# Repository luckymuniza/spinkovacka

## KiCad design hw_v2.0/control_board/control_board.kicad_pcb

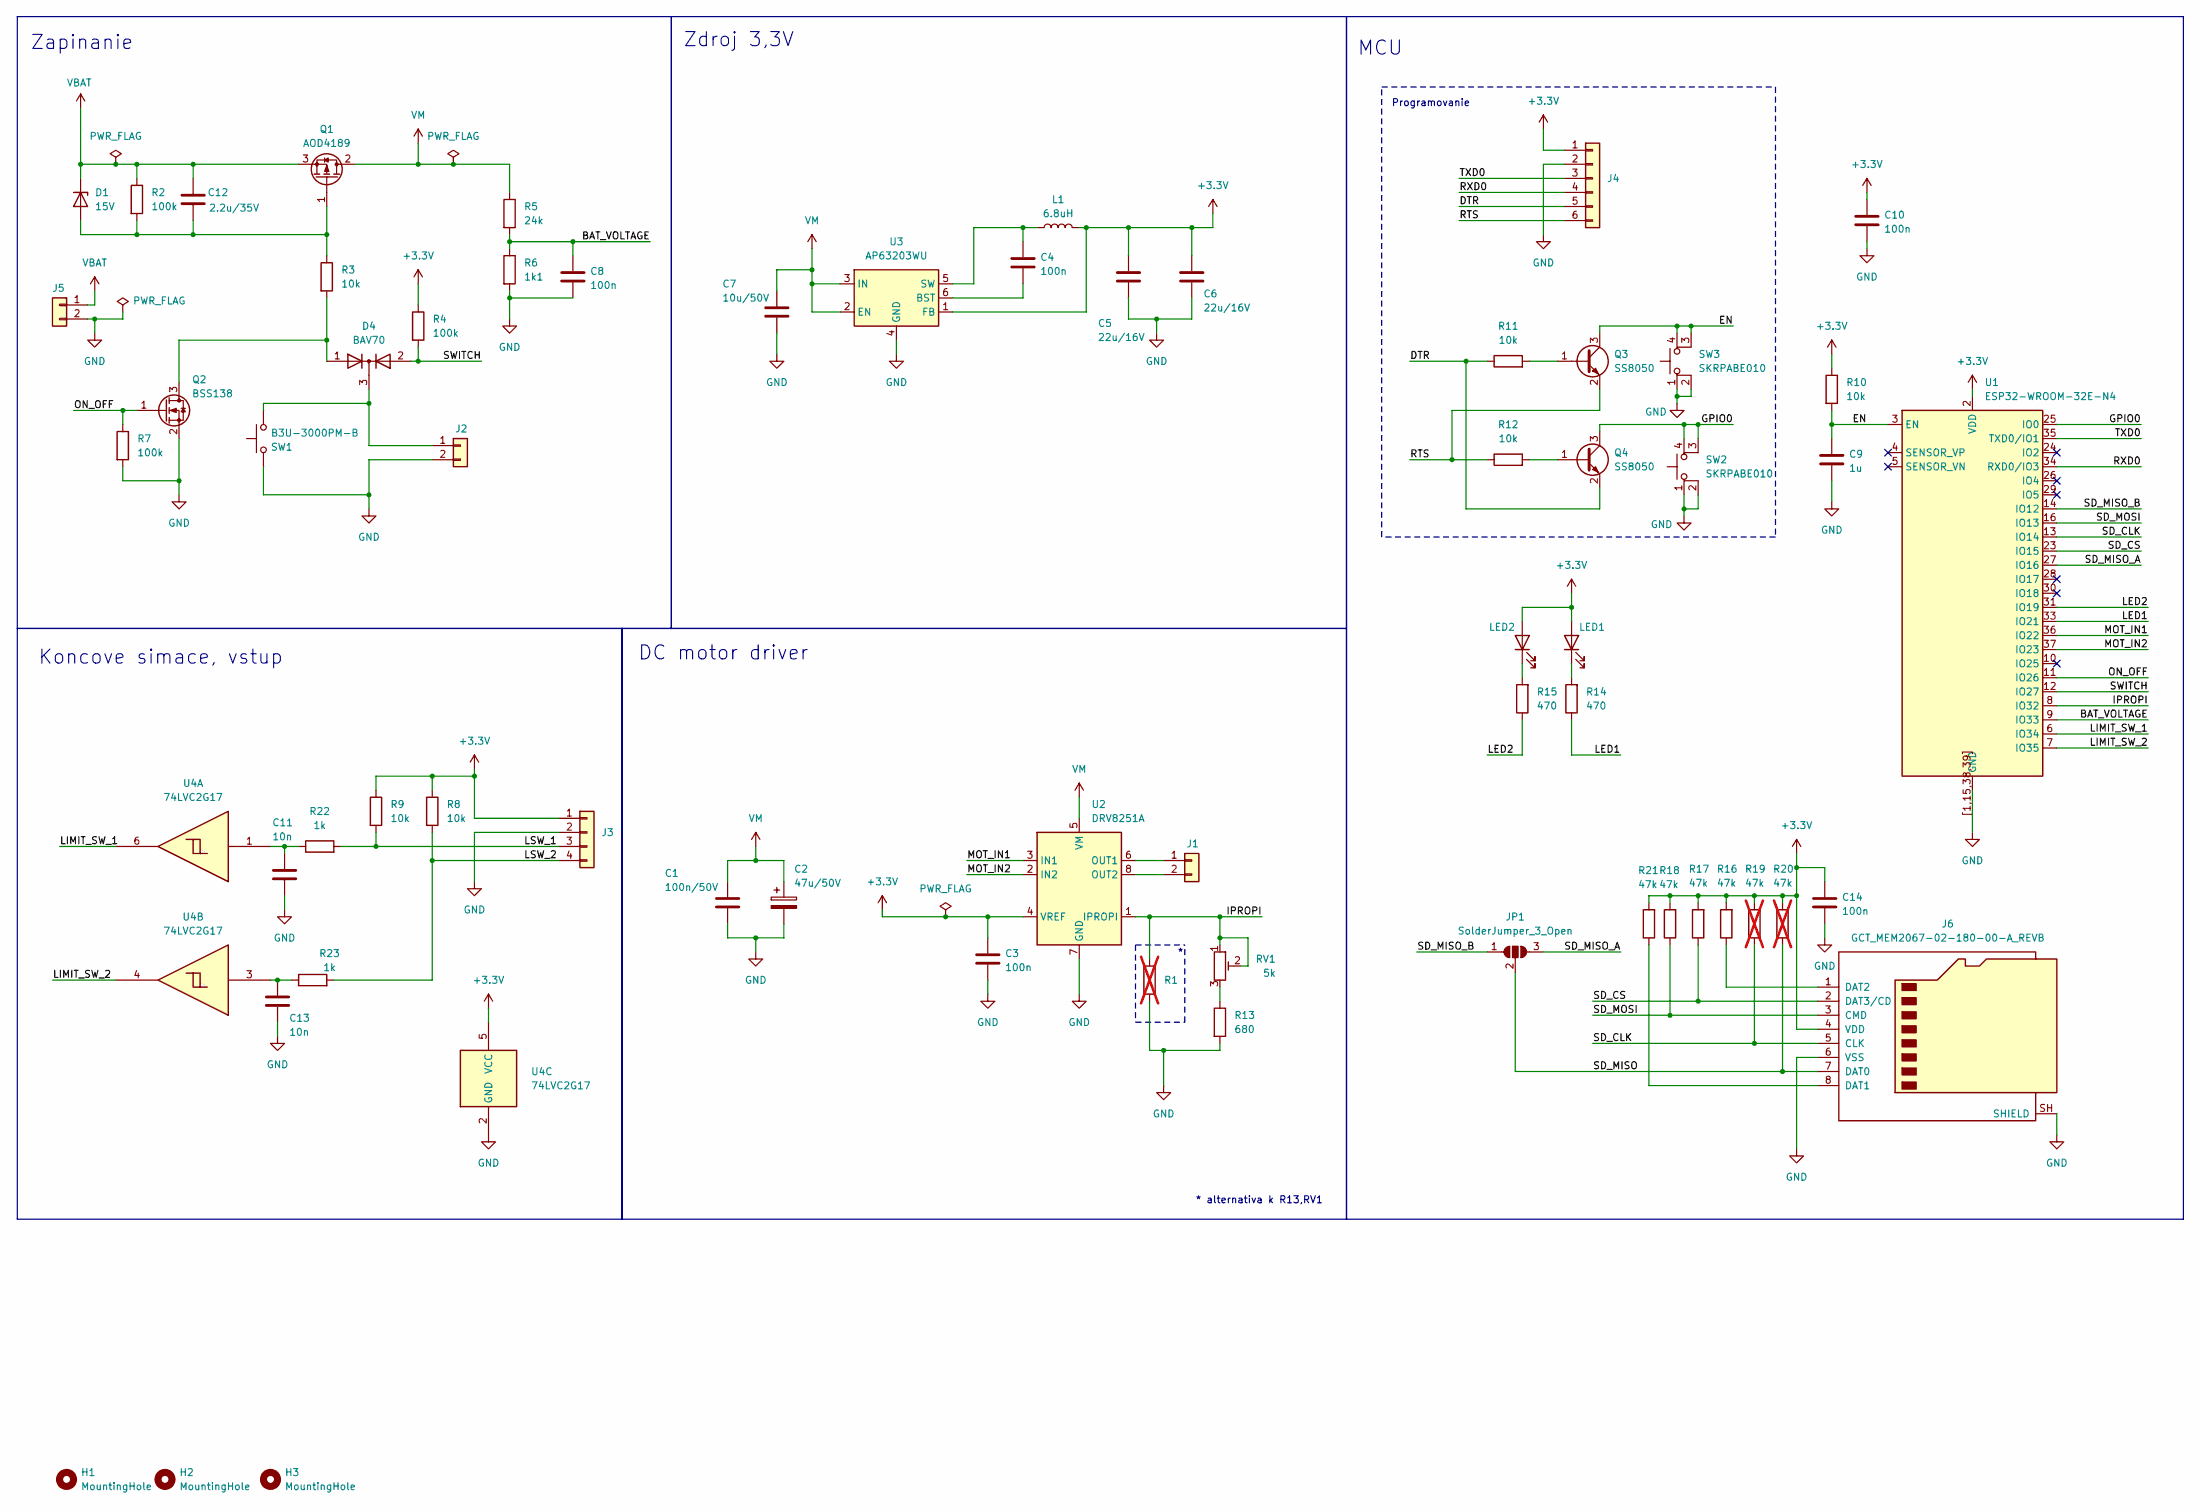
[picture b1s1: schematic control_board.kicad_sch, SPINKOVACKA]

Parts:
C1: 100n/50V; C_1206_3216Metric
C2: 47u/50V; CP_Elec_6.3x5.8
C3, C4, C8, C10: 100n; C_1206_3216Metric
C5, C6: 22u/16V; C_1206_3216Metric
C7: 10u/50V; C_1210_3225Metric
C9: 1u; C_1206_3216Metric
C11, C13: 10n; C_0805_2012Metric
C12: 2.2u/35V; C_1206_3216Metric
C14: 100n; C_0805_2012Metric_Pad1.18x1.45mm_HandSolder
D1: 15V; Nexperia_CFP3_SOD-123W
D4: BAV70; SOT-23
H1, H2, H3: MountingHole; MountingHole_3.2mm_M3
J1: JST_XH_B2B-XH-A_1x02_P2.50mm_Vertical
J2: JST_PH_B2B-PH-K_1x02_P2.00mm_Vertical
J3: JST_PH_B4B-PH-K_1x04_P2.00mm_Vertical
J4: JST_PH_B6B-PH-K_1x06_P2.00mm_Vertical
J5: JST_VH_B2PS-VH_1x02_P3.96mm_Horizontal
J6: GCT_MEM2067-02-180-00-A_REVB
JP1: SolderJumper_3_Open; SolderJumper-3_P1.3mm_Open_RoundedPad1.0x1.5mm_NumberLabels
L1: 6.8uH; L_Panasonic_PCC-M0530M
LED1, LED2: LED_1206_3216Metric
Q1: AOD4189; TO-252-2
Q2: BSS138; SOT-23
Q3, Q4: SS8050; SOT-23
R1: 1k5; R_0805_2012Metric; not fitted
R2, R4, R7: 100k; R_0805_2012Metric
R3, R8, R9, R10, R11, R12: 10k; R_0805_2012Metric
R5: 24k; R_0805_2012Metric
R6: 1k1; R_0805_2012Metric
R13: 680; R_0805_2012Metric
R14, R15: 470; R_0805_2012Metric
R16, R17, R18, R21: 47k; R_0805_2012Metric
R19, R20: 47k; R_0805_2012Metric; not fitted
R22, R23: 1k; R_0805_2012Metric
RV1: 5k; Potentiometer_Bourns_3314J_Vertical
SW1: B3U-3000PM-B; SW_SPST_B3U-3000P-B
SW2, SW3: SKRPABE010; SW_TACT_ALPS_SKRPABE010
U1: ESP32-WROOM-32E-N4; ESP32-WROOM-32E
U2: DRV8251A; SOIC-8-1EP_3.9x4.9mm_P1.27mm_EP2.95x4.9mm_Mask2.71x3.4mm_Th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
U3: AP63203WU; TSOT-23-6
U4: 74LVC2G17; SOT-23-6

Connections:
+3.3V: C3.1, C5.1, C6.1, C10.1, C14.1, J3.1, J4.1, J6.4 (VDD), L1.2, LED1.2 (A), LED2.2 (A), R4.1, R8.1, R9.1, R10.1, R16.2, R17.2, R18.2, R19.2, R20.2, R21.2, U1.2 (VDD), U2.4 (VREF), U3.1 (FB), U4.5 (VCC)
/BAT_VOLTAGE: C8.1, R5.2, R6.1, U1.9 (IO33)
/DTR: J4.5, Q4.2 (E), R11.1
/EN: C9.1, Q3.3 (C), R10.2, SW3.3 (K), SW3.4 (A), U1.3 (EN)
/GPIO0: Q4.3 (C), SW2.3 (K), SW2.4 (A), U1.25 (IO0)
/IPROPI: R1.1, RV1.1, RV1.2, U1.8 (IO32), U2.1 (IPROPI)
/LED1: R14.1, U1.33 (IO21)
/LED2: R15.1, U1.31 (IO19)
/LIMIT_SW_1: U1.6 (IO34), U4.6
/LIMIT_SW_2: U1.7 (IO35), U4.4
/LSW_1: J3.3, R9.2, R22.2
/LSW_2: J3.4, R8.2, R23.2
/MOT_IN1: U1.36 (IO22), U2.3 (IN1)
/MOT_IN2: U1.37 (IO23), U2.2 (IN2)
/ON_OFF: Q2.1 (G), R7.1, U1.11 (IO26)
/RTS: J4.6, Q3.2 (E), R12.1
/RXD0: J4.4, U1.34 (RXD0/IO3)
/SD_CLK: J6.5 (CLK), R19.1, U1.13 (IO14)
/SD_CS: J6.2 (DAT3/CD), R17.1, U1.23 (IO15)
/SD_MISO: J6.7 (DAT0), JP1.2 (C), R20.1
/SD_MISO_A: JP1.3 (B), U1.27 (IO16)
/SD_MISO_B: JP1.1 (A), U1.14 (IO12)
/SD_MOSI: J6.3 (CMD), R18.1, U1.16 (IO13)
/SWITCH: D4.2 (A), R4.2, U1.12 (IO27)
/TXD0: J4.3, U1.35 (TXD0/IO1)
GND: C1.2, C2.2, C3.2, C5.2, C6.2, C7.2, C8.2, C9.2, C10.2, C11.2, C13.2, C14.2, J2.2, J3.2, J4.2, J5.2, J6.6 (VSS), J6.SH (SHIELD), Q2.2 (S), R1.2, R6.2, R7.2, R13.2, SW1.2, SW2.1, SW2.2, SW3.1, SW3.2, U1.1 (GND), U1.15 (GND), U1.38 (GND), U1.39 (GND), U1.[1,15,38,39] (GND), U2.7 (GND), U2.9 (GND), U3.4 (GND), U4.2 (GND)
unnamed: C11.1, R22.1, U4.1
unnamed: C13.1, R23.1, U4.3
unnamed: C12.2, D1.2 (A), Q1.1 (G), R2.2, R3.1
unnamed: D4.3 (K), J2.1, SW1.1
unnamed: J1.1, U2.6 (OUT1)
unnamed: J1.2, U2.8 (OUT2)
unnamed: J6.8 (DAT1), R21.1
unnamed: J6.1 (DAT2), R16.1
unnamed: LED1.1 (K), R14.2
unnamed: LED2.1 (K), R15.2
unnamed: D4.1 (A), Q2.3 (D), R3.2
unnamed: Q3.1 (B), R11.2
unnamed: Q4.1 (B), R12.2
unnamed: R13.1, RV1.3
unnamed: C4.2, U3.6 (BST)
unnamed: C4.1, L1.1, U3.5 (SW)
VBAT: C12.1, D1.1 (K), J5.1, Q1.3 (S), R2.1
VM: C1.1, C2.1, C7.1, Q1.2 (D), R5.1, U2.5 (VM), U3.2 (EN), U3.3 (IN)

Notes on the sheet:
MCU
Zapinanie
Zdroj 3,3V
Koncove simace, vstup
Programovanie
DC motor driver
* alternativa k R13,RV1

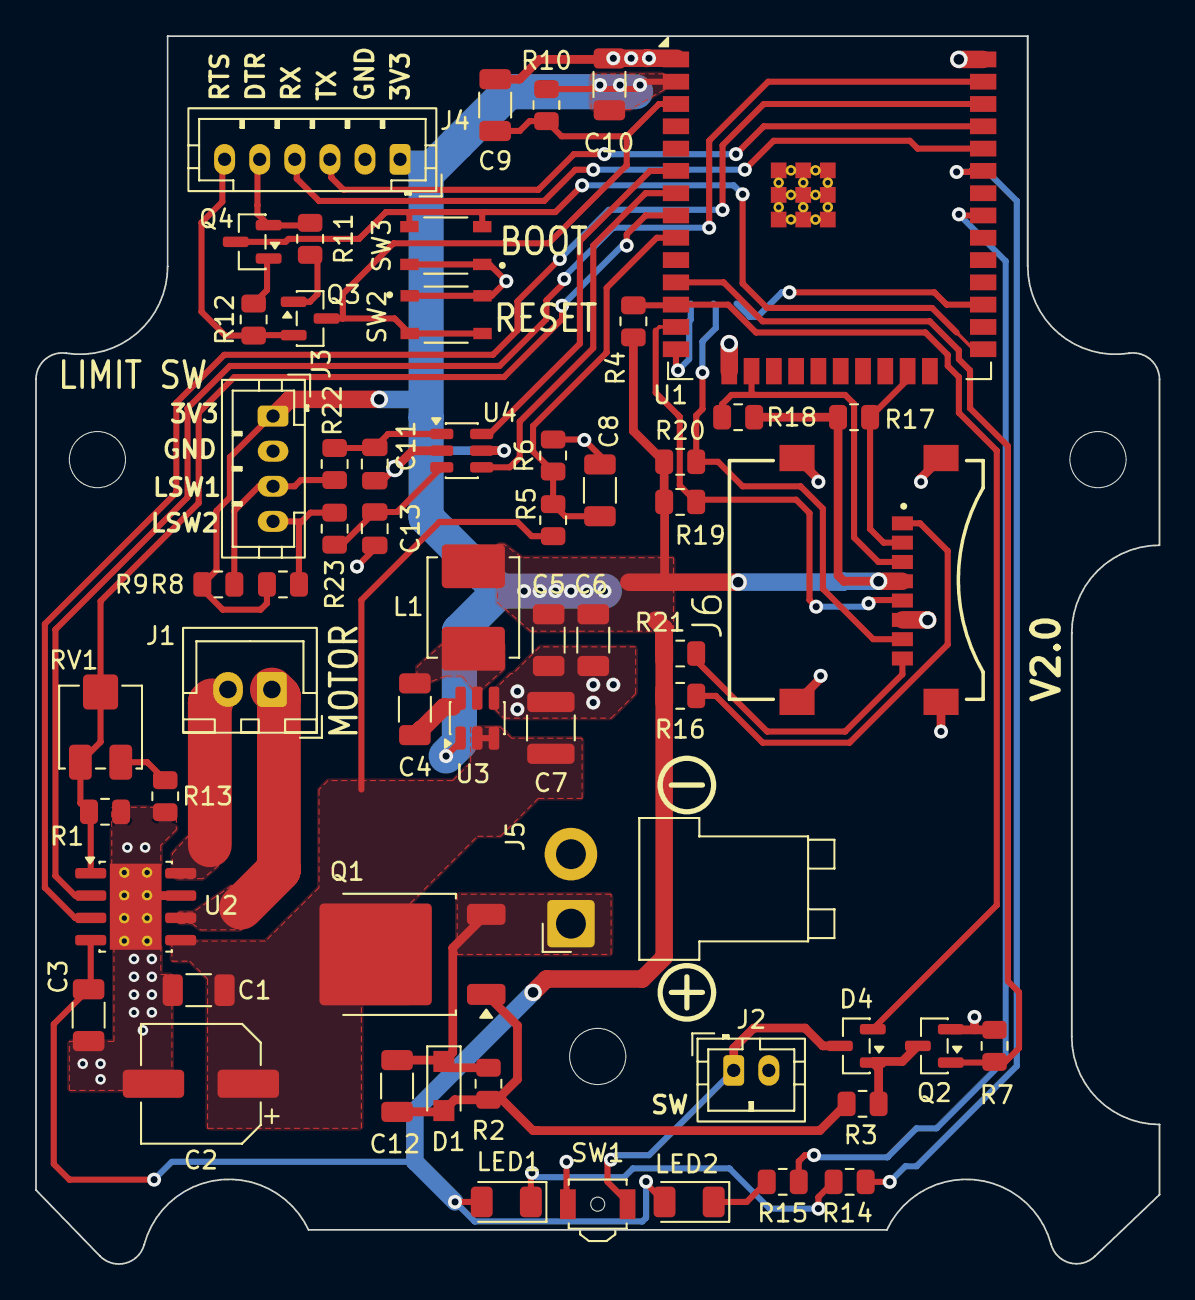
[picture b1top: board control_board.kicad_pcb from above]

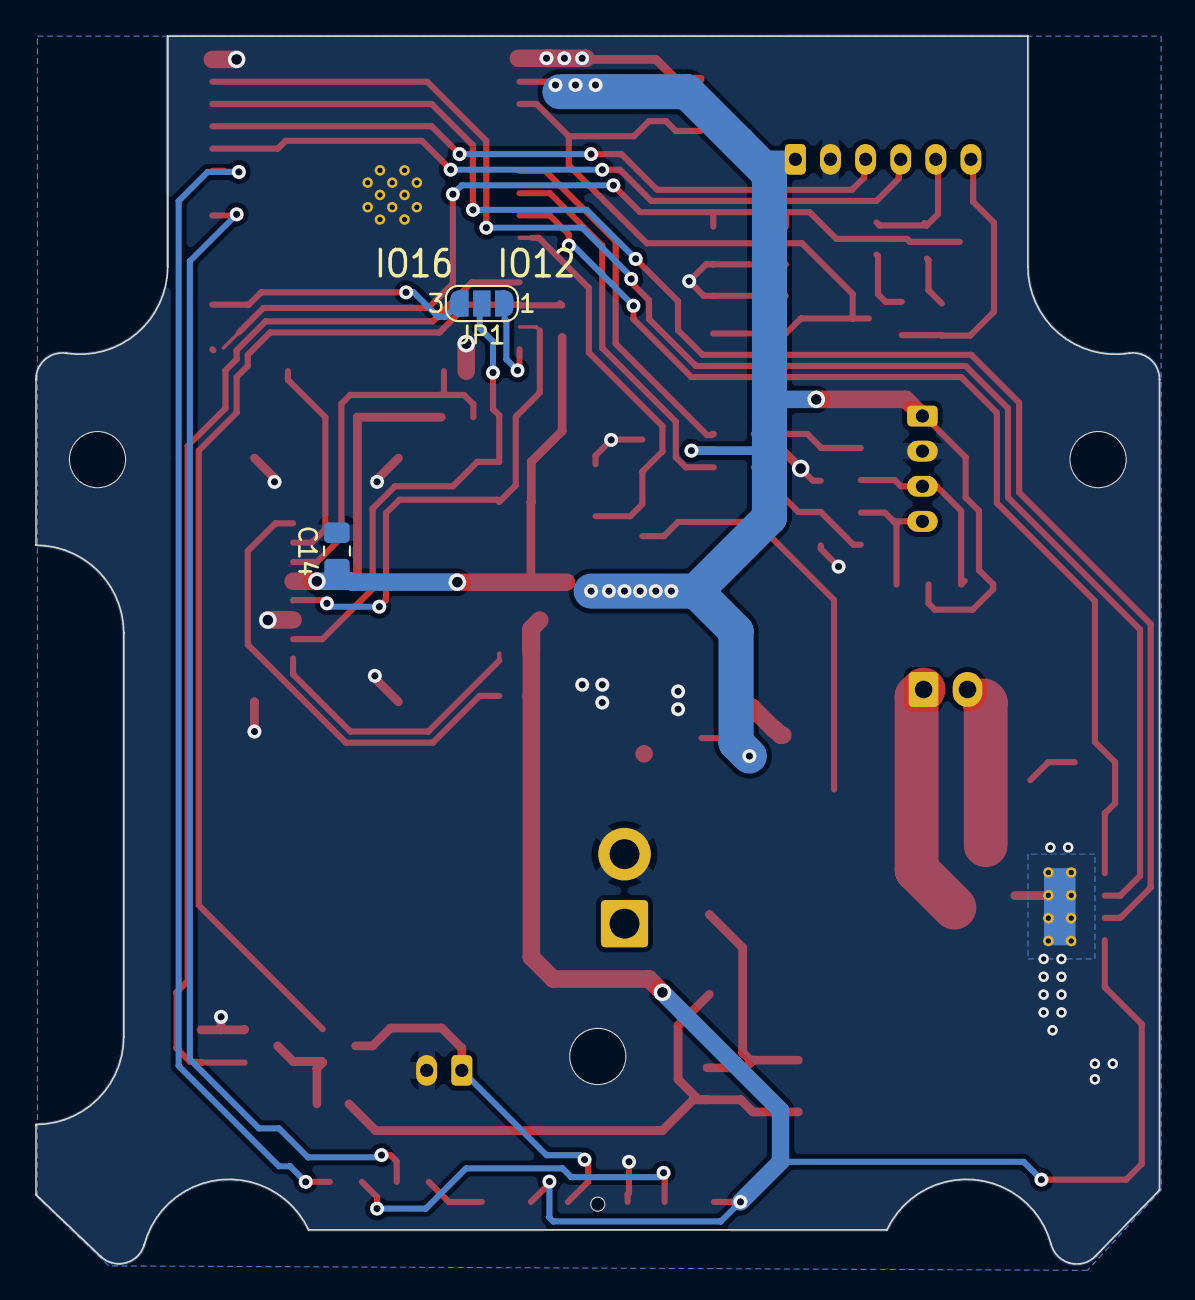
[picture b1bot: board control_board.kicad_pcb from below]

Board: 2 copper layers, 64.0 x 69.9 mm, 64 parts (2 on the bottom side), 44 nets.

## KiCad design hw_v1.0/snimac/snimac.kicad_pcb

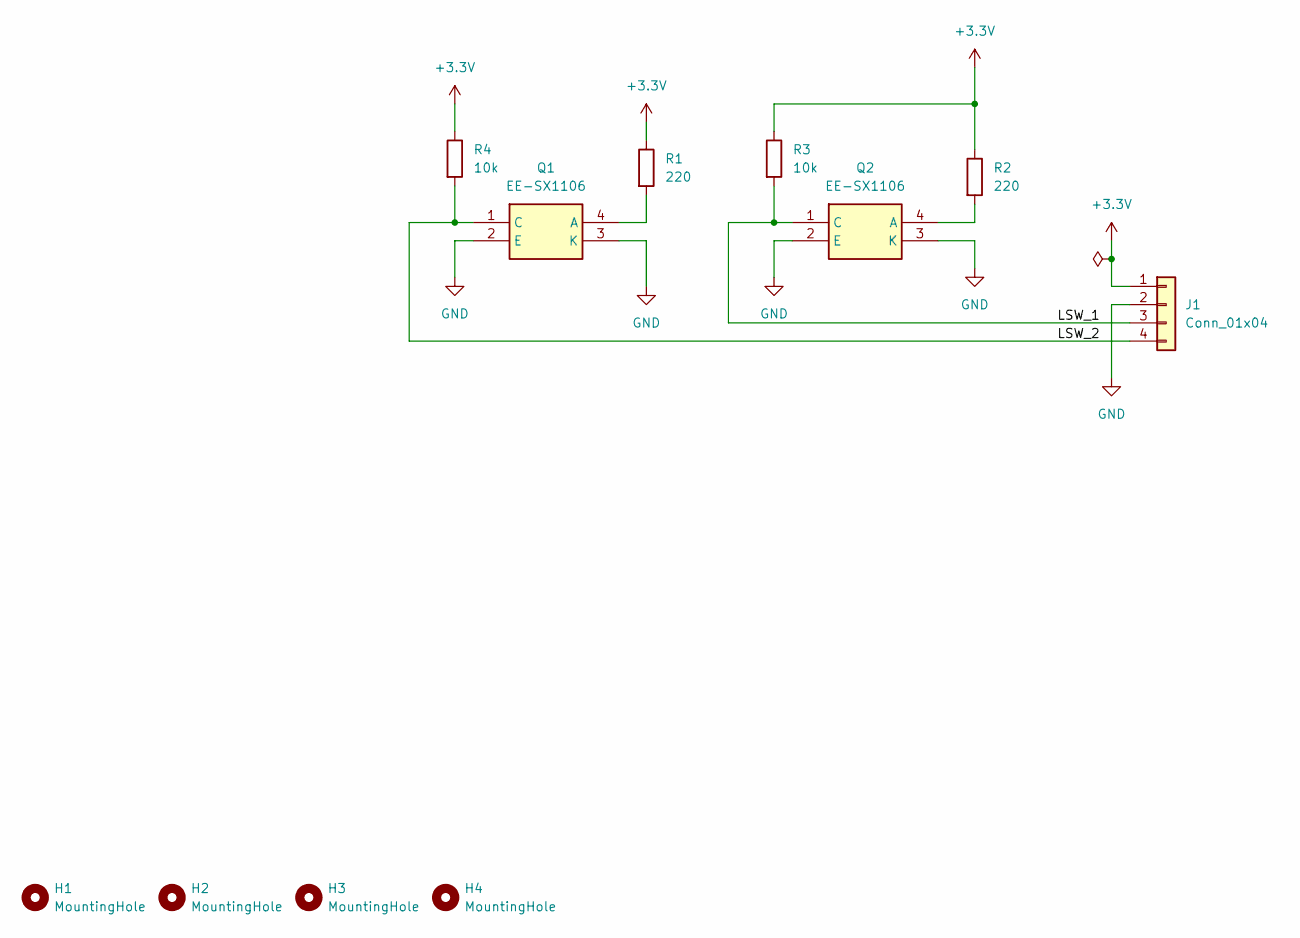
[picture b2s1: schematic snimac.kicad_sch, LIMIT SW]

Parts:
H1, H2, H3, H4: MountingHole; MountingHole_2.5mm
J1: Conn_01x04; JST_PH_B4B-PH-K_1x04_P2.00mm_Vertical
Q1, Q2: EE-SX1106; EESX1106; Manufacturer_Part_Number EE-SX1106; Mouser Part Number 653-EE-SX1106
R1, R2: 220; R_0805_2012Metric_Pad1.20x1.40mm_HandSolder
R3, R4: 10k; R_0805_2012Metric_Pad1.20x1.40mm_HandSolder

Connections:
+3.3V: J1.1, R1.1, R2.1, R3.1, R4.1
/LSW_1: J1.3, Q2.1 (C), R3.2
/LSW_2: J1.4, Q1.1 (C), R4.2
GND: J1.2, Q1.2 (E), Q1.3 (K), Q2.2 (E), Q2.3 (K)
unnamed: Q1.4 (A), R1.2
unnamed: Q2.4 (A), R2.2

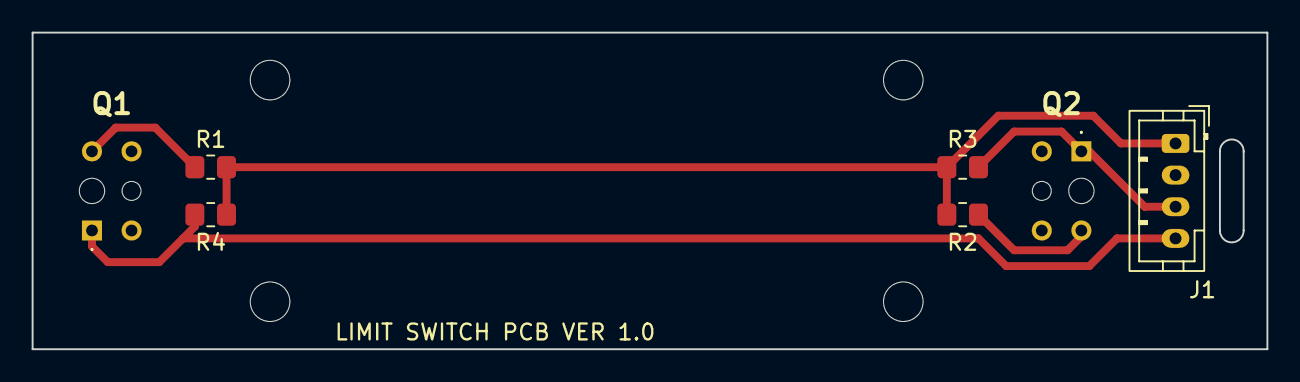
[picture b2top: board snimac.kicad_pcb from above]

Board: 2 copper layers, 78.0 x 20.0 mm, 11 parts (0 on the bottom side), 6 nets.

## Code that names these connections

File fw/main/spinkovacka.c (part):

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/* ----------------------------- Piny ------------------------------------- */
#define LED_BATT_GPIO           21       /*LED pin pre zobrazenie stavu baterie */
#define LED_MODE_GPIO           19       /*LED pin pre zobrazenie stavu - vypinanie, mod BT/WIFI */
#define MOT_IN1_GPIO            22       /* PWM vystup (LEDC) */
#define MOT_IN2_GPIO            23       /* riadenie motora 2. vstup, stale = 1*/
#define ONOFF_GPIO              26       /* vystup - zapnutie napajania*/
#define ONOFF_BUTTON_GPIO       27       /* tlacitko , zapnutie, vypnutie, zmena modu*/
#define IPROPI_GPIO             32       /* ADC1_CH4 */
#define BAT_VOLT_GPIO           33       /* ADC1_CH5 */
#define LIMIT_SW_1_GPIO         35       //sw1 - spusta motor
#define LIMIT_SW_2_GPIO         34       //sw2 - vypina motor
//SD karta (SPI)
#define SD_MOSI_GPIO            13
#define SD_CLK_GPIO             14
#define SD_CS_GPIO              15
#define SD_MISO_GPIO            16

//ADC pouzite kanaly
#define IPROPI_ADC_CH      ADC_CHANNEL_4
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

#define BAT_VOLT_DIVIDER_RATIO    22.8181f   /* Vbat/Vadc pomer odporoveho delica R5,R6 (R5+R6)/R6 */
#define IPROPI_FULL_SCALE_V       3.3f     /* IPROPI je priamo napatie 0..3.3 V */

#define BATTERY_LOW_LEVEL_V        16.0f  //napatie ked zacne blikat led
#define BATTERY_CRITICAL_LEVEL_V   12.0f  //napatie ked sa uz nespusti motor
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}


/* Brzda: duty 0 % -> (invertovany vystup) MOT_IN1 = 1
 * vola sa ked treba motor zabrzdit
 */
static void motor_brake(void) {
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    ESP_ERROR_CHECK(ledc_timer_config(&tcfg));

    ledc_channel_config_t ccfg = {
        .gpio_num   = MOT_IN1_GPIO,
        .speed_mode = LEDC_MODE,
        .channel    = LEDC_CHANNEL,
        .timer_sel  = LEDC_TIMER,
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    /* Digitalne vystupy: LED1, LED2, MOT_IN2, ON_OFF (MOT_IN1 nastavi LEDC PWM controler) */
    gpio_config_t out = {
        .pin_bit_mask = (1ULL << LED_BATT_GPIO) | (1ULL << LED_MODE_GPIO) |
                        (1ULL << MOT_IN2_GPIO) | (1ULL << ONOFF_GPIO),
        .mode         = GPIO_MODE_INPUT_OUTPUT, //aj input aby sa dal precitat stav pinu (koli led blikaniu)
        .pull_up_en   = GPIO_PULLUP_DISABLE,
        .pull_down_en = GPIO_PULLDOWN_DISABLE,
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    /* vychodzie stavy */
    gpio_set_level(LED_BATT_GPIO, 1);      /* LED zhasnuta */
    gpio_set_level(LED_MODE_GPIO, 1);      /* LED zhasnuta */
    gpio_set_level(MOT_IN2_GPIO, 1);   /* trvalo 1 */
    gpio_set_level(ONOFF_GPIO, 1);    /* drzi napajanie zopnute */

    /* SWITCH: vstup s internym pull-up (stlacene = 0) */
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    /* LIMIT_SW_1/2: vstupy, cisty signal (opticka zavora + Schmitt),
     * netreba interne pull up. */
    gpio_config_t lim = {
        .pin_bit_mask = (1ULL << LIMIT_SW_1_GPIO) | (1ULL << LIMIT_SW_2_GPIO),
        .mode         = GPIO_MODE_INPUT,
        .pull_up_en   = GPIO_PULLUP_DISABLE,
        .pull_down_en = GPIO_PULLDOWN_DISABLE,
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 * ak je vstup 0 -> je opticka zavora neaktivna
 */
static inline bool limit_sw1_active(void) {
    return gpio_get_level(LIMIT_SW_1_GPIO) == 1;
}
static inline bool limit_sw2_active(void) {
    return gpio_get_level(LIMIT_SW_2_GPIO) == 1;
}


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    float v = battery_raw_to_volt(g_battery_volt_raw);

    spi_bus_config_t bus_cfg = {
        .mosi_io_num     = SD_MOSI_GPIO,
        .miso_io_num     = SD_MISO_GPIO,
        .sclk_io_num     = SD_CLK_GPIO,
        .quadwp_io_num   = -1,
        .quadhd_io_num   = -1,
        .max_transfer_sz = 4000,
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    sdmmc_host_t host = SDSPI_HOST_DEFAULT();
    host.slot = SD_SPI_HOST;
    sdspi_device_config_t slot_cfg = SDSPI_DEVICE_CONFIG_DEFAULT();
    slot_cfg.gpio_cs = SD_CS_GPIO;
    slot_cfg.host_id = SD_SPI_HOST;

    esp_vfs_fat_sdmmc_mount_config_t mount_cfg = {
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 * motor sa spusti ak sa aktiviuje LIMIT_SW_1 a bateria je v stave OK, alebo LOW
 * vypne sa ked sa aktivuje LIMIT_SW_2, ale pocka este LIMIT_SW2_BRAKE_DELAY_MS, potom sa vypne
 * snima sa hrana signalu.
 * Po spusteni spinkovaca sa motor automaticky spusti. Naspusti sa len v pripade ze je aktivny LIMIT_SW_2.
  */

static void motor_control_task(void *arg)
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                if (dur_us >= CHANGE_MODE_HOLD_US ) {
                    /* >6 s: vstup do mode rezimu */
                    g_wifi_mode_active = true;
                    gpio_set_level(LED_MODE_GPIO, 0);   /* LED2 svieti */
                    ESP_LOGI(TAG, "BT/WiFi mode ON");
                    /* TODO: zapnut BT/WiFi a spustit BT/WIFI mode funkcionalitu */

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                if (dur_us >= CHANGE_MODE_HOLD_US ) {
                    /* >6 s: navrat z mode rezimu */
                    g_wifi_mode_active = false;
                    gpio_set_level(LED_MODE_GPIO, 1);   /* LED2 zhasne */
                    //TODO: vypnut BT/WIFI


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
